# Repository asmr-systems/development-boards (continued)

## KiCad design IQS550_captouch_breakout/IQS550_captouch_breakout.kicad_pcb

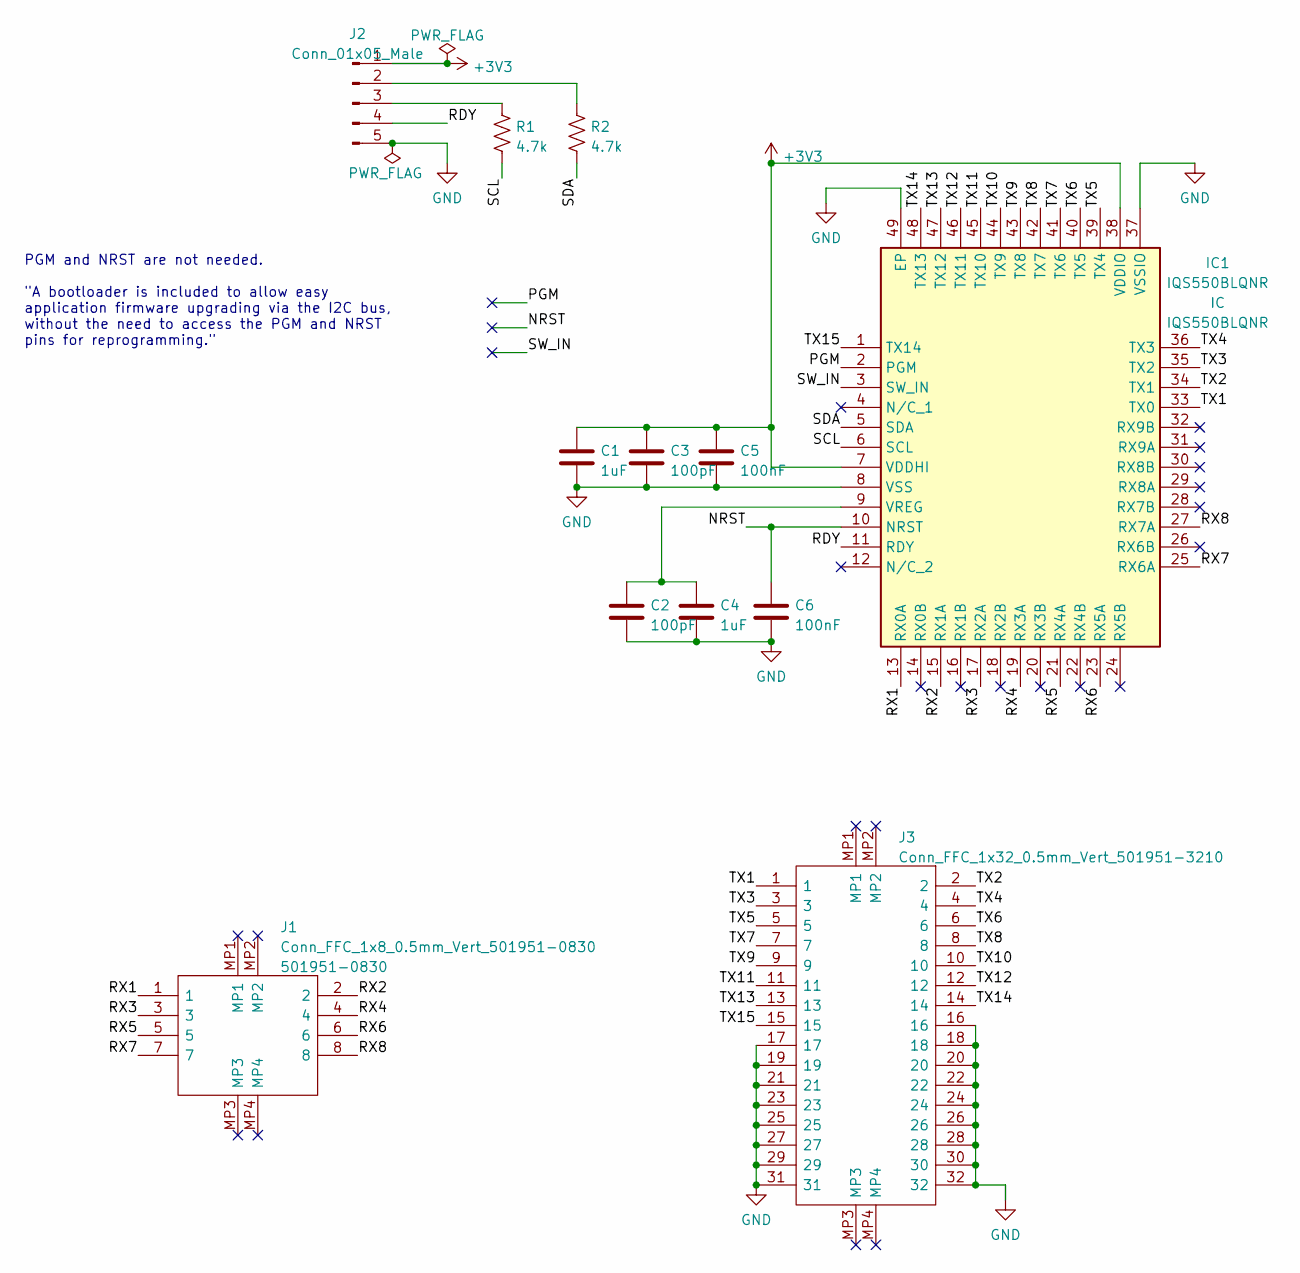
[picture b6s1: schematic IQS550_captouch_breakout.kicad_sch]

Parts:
C1, C4: 1uF; C_0805_2012Metric
C2, C3: 100pF; C_0805_2012Metric
C5, C6: 100nF; C_0805_2012Metric
IC1: IQS550BLQNR; QFN50P700X700X60-49N-D; Mouser Part Number N/A
J1: Conn_FFC_1x8_0.5mm_Vert_501951-0830; Conn_FFC_1x8_0.5mm_Molex_5019510830; Mouser Part Number 538-501951-0830
J2: Conn_01x05_Male; PinHeader_1x05_P2.54mm_Vertical
J3: Conn_FFC_1x32_0.5mm_Vert_501951-3210; Conn_FFC_1x32_0.5mm_Molex_5019513210; Mouser Part Number 538-501951-3210
R1, R2: 4.7k; R_0805_2012Metric

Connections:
+3V3: C1.1, C3.1, C5.1, IC1.7 (VDDHI), IC1.38 (VDDIO), J2.1
/NRST: C6.1, IC1.10 (NRST)
/PGM: IC1.2 (PGM)
/RDY: IC1.11 (RDY), J2.4
/RX1: IC1.13 (RX0A), J1.1
/RX2: IC1.15 (RX1A), J1.2
/RX3: IC1.17 (RX2A), J1.3
/RX4: IC1.19 (RX3A), J1.4
/RX5: IC1.21 (RX4A), J1.5
/RX6: IC1.23 (RX5A), J1.6
/RX7: IC1.25 (RX6A), J1.7
/RX8: IC1.27 (RX7A), J1.8
/SCL: IC1.6 (SCL), R1.2
/SDA: IC1.5 (SDA), R2.2
/SW_IN: IC1.3 (SW_IN)
/TX1: IC1.33 (TX0), J3.1
/TX2: IC1.34 (TX1), J3.2
/TX3: IC1.35 (TX2), J3.3
/TX4: IC1.36 (TX3), J3.4
/TX5: IC1.39 (TX4), J3.5
/TX6: IC1.40 (TX5), J3.6
/TX7: IC1.41 (TX6), J3.7
/TX8: IC1.42 (TX7), J3.8
/TX9: IC1.43 (TX8), J3.9
/TX10: IC1.44 (TX9), J3.10
/TX11: IC1.45 (TX10), J3.11
/TX12: IC1.46 (TX11), J3.12
/TX13: IC1.47 (TX12), J3.13
/TX14: IC1.48 (TX13), J3.14
/TX15: IC1.1 (TX14), J3.15
unnamed: C2.1, C4.1, IC1.9 (VREG)
unnamed: J2.2, R2.1
unnamed: J2.3, R1.1

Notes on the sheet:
PGM and NRST are not needed. "A bootloader is included to allow easy application firmware upgrading via the I2C bus, without the need to access the PGM and NRST pins for reprogramming."

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
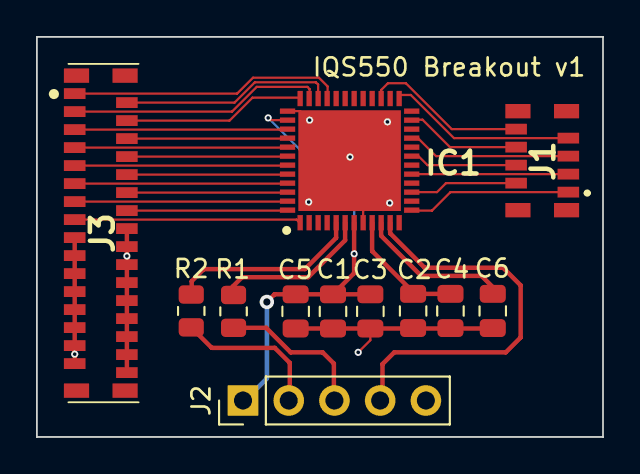
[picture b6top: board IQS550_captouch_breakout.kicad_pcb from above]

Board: 2 copper layers, 31.4 x 22.2 mm, 12 parts (0 on the bottom side), 32 nets.

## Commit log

2021-11-27 add samd10 dev board kicad files
2021-11-30 adding pcb layout for samd10 board
2021-12-07 finished samd10 pipsqueek v0 (ordered)
2022-01-10 fix samd10 pipsqueek dev board, update footprint for usbc receptacle/power reg symbol name, generate gerbers/drill files
2022-01-12 beginning samd51 dev board schematic
2022-01-14 finish asmr bunny hop board
2022-01-14 export bunny hop schematic in pdf form
2022-01-15 finished samd21 dev board (syzygy), exported gerbers and drill files
2022-01-26 updated SAMD51 (BUNNYHOP) BOM
2022-02-04 add eurorack_to_3v3 board, almost complete
2022-02-05 finish first pass of schematic. need to look everything over again
2022-02-05 finished Big On, Little One schematic. Generated BOM. Now PCB Layout
2022-02-05 update op amps to have power supply
2022-02-06 update manufacturer part number for each component
2022-02-07 assign most footprints except banana jacks...need to figure out a good connection approach
2022-02-10 update wire-to-board connectors instead of banana plugs, begin pcb layout
2022-02-11 continuing Big One Little One PCB layout
2022-02-11 finished input stages PCB layout
2022-02-13 finished pcb layout, just a few bugs from rules checker
2022-02-13 fixed clearance issues with pcb
2022-02-13 finished pcb, time to order
2022-03-04 save in newer kicad format, and begin soldering
2022-03-06 add soldering progress notes
2022-03-07 update sioldering log
2022-04-26 add notes on hardware debugging status
2022-04-26 fix gate_to_3v3 schematic
2022-04-27 add BH2227 breakout board
2022-05-02 update schematic for eurorack_to_3v, add BH2227 pcb layout
2022-05-03 update eurorack_to_3v3 schematic for v2
2022-05-03 pcb refactor in progress
2022-05-04 finished Big One Little One v2
2022-05-04 cleanup tracks
2022-05-04 cleanup and add gerbers
2022-09-14 add at42qt touch sensor dev board
2022-09-14 almost complete at42qt pcb layout
2022-09-15 finish designing touch sensor dev board
2022-09-15 generated jlcpcb gerbers
2022-09-16 starting led matrix board
2022-09-17 finished led grid schematic
2022-09-17 create grid template dfx
2022-09-19 complete hald of led matrix pcb layout
2022-09-22 add led matrix gerbers (jlcpcb)
2023-01-23 create opamp breakout board
2023-01-24 added copper fill to pcb
2023-02-28 add interleaved cap touch sensor board
2023-03-24 added experimental captouch boards
2023-03-30 almost complete IQS550 breakout schematic
2023-03-31 finished IQS550 pcb
2023-04-11 added interactive bom for IQS550 board
2023-05-15 added cap touch padded interleaved sensor boards
2023-05-26 begin new high resolution cap touch surface experiment
2023-05-30 added new high resolution touch boards
2023-06-22 added new captouch boards
2023-08-01 finish 256 self cap touch board
2023-08-01 print 256 self cap touch board and fpc breakout
